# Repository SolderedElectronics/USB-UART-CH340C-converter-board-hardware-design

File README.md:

# USB-UART CH340 converter board Hardware Design

## About the Product

|  |
| :----------------------------------------------------------: |
| [Buy USB-UART CH340 converter board](https://www.solde.red/333028) |

This small USBUART adapter converts USB communication into UART (serial) communication, and everything you might need is already on this small board. In addition to the classic UART pins that are arranged in the standard layout: DTR, RXD, TXD, VCC, CTS, GND, other pins available of the CH340 chip are also available on header: RS232, RI, DCD, DSR, RST and CTS. Indication LEDs show activity on RXT and TXD lines, and a 500mA fuse protects this programmer, the USB port of the computer that is connected, and other devices connected to it from damage.

Additionally, there is a voltage regulator and a switch on the board, and it is possible to choose the output voltage of 3.3V or 5V, depending on the device you are using. The logic of the UART signal is always 3.3V, but don’t worry, 5V devices will work with 3V3 UART logic without any problems. Use a USB-C cable to connect.

---

## Repository Contents

This repository contains all design files for USB-UART CH340 converter board, organized as follows:

- **`CAD` folder**: Contains KiCAD design files, including:
  - Schematics
  - PCB layout
  - Panel PCB layout
  - Source 3D files in Fusion360, if any
  - All files are sorted by version with a detailed change log.
- **`OUTPUTS` folder**: Includes all production-ready files, such as:
  - Bill of Materials (BOM) and interactive BOM (iBOM)
  - PDF versions of schematics
  - 3D `.step` file of the board
  - 3D-printable models
  - Gerber files for PCB manufacturing
  - Image of the pinout of the board
  - Product image
  - Compliance, legal and generic sales documents

Refer to the `Change Log` in the CAD folder for details about updates between versions.

---

## Learn More About the Product

Beyond the repository, explore the following resources:

### Soldered Verify

The **Soldered Verify** system ensures every board you purchase from Soldered is fully functional. It also provides access to exclusive test data for your product. To get started, find the unique Soldered Verify ID on your product's packaging and enter the ID on the [Soldered Verify page](https://soldered.com/verify/) to access test results and additional product details.

### Soldered Community

Soldered Community is your go-to place for technical support. Our engineers track and answer all questions posted there, and it’s a great space for the maker community. Get answers to your questions and solutions for your challenges at [Soldered Community](https://soldered.com/community).

### solde.red

solde.red is an ultimate URL shortener and information hub. Access it by typing solde.red/ followed by your product SKU, e.g., [solde.red/333000](https://solde.red/333000), to find getting-started guides, datasheets, open-source hardware and software files, certifications, images, pinouts, and more. Read more about the shortener [here](https://solde.red/info/).

---

## Contributing

Contributions are welcome! Here’s how you can get involved:

- Submit pull requests to enhance the design or fix issues.
- Report bugs or problems by opening an issue.

We encourage community collaboration to make this product even better.

---

## About Soldered

[Soldered for Makers](https://soldered.com) specializes in designing and manufacturing electronic products tailored for enthusiasts, ranging from hobbyists to professionals. Our portfolio includes electronic boards, sensors, and actuators that are widely utilized in fields such as microelectronics, mechatronics, robotics, programming, and IoT. Every product we offer is designed in-house and built upon open-source hardware and software platforms. Proudly certified and manufactured within the European Union, our catalog likely includes the product you need for your project.

We complement these products with comprehensive tutorials and manuals, product descriptions, schematics, programming codes, and project examples. Our round-the-clock [customer and technical support](https://soldered.com/community) is available for all our products, irrespective of the sales channel. Soldered’s success and services reflect our maker community’s unwavering [trust](https://www.trustpilot.com/review/soldered.com), for which we are deeply grateful. Join our community and create using Soldered products.

---

## License

All Soldered open-source hardware (OSH) is under The TAPR Open Hardware License. Read more in the LICENSE file located in this repository.

**Disclaimer:**

No warranty - all designs in this repository are distributed in the hope that they will be useful, but without any warranty. They are provided "AS IS", therefore without warranty of any kind, either expressed or implied. The entire quality and performance of what you do with the contents of this repository are your responsibility. In no event Soldered Electronics will be liable for your damages, or losses, including any general, special, incidental, or consequential damage arising out of the use or inability to use the contents of this repository. 

---

## Have fun!

Thank you for your support from your fellow makers at Soldered Electronics.

Happy Making!

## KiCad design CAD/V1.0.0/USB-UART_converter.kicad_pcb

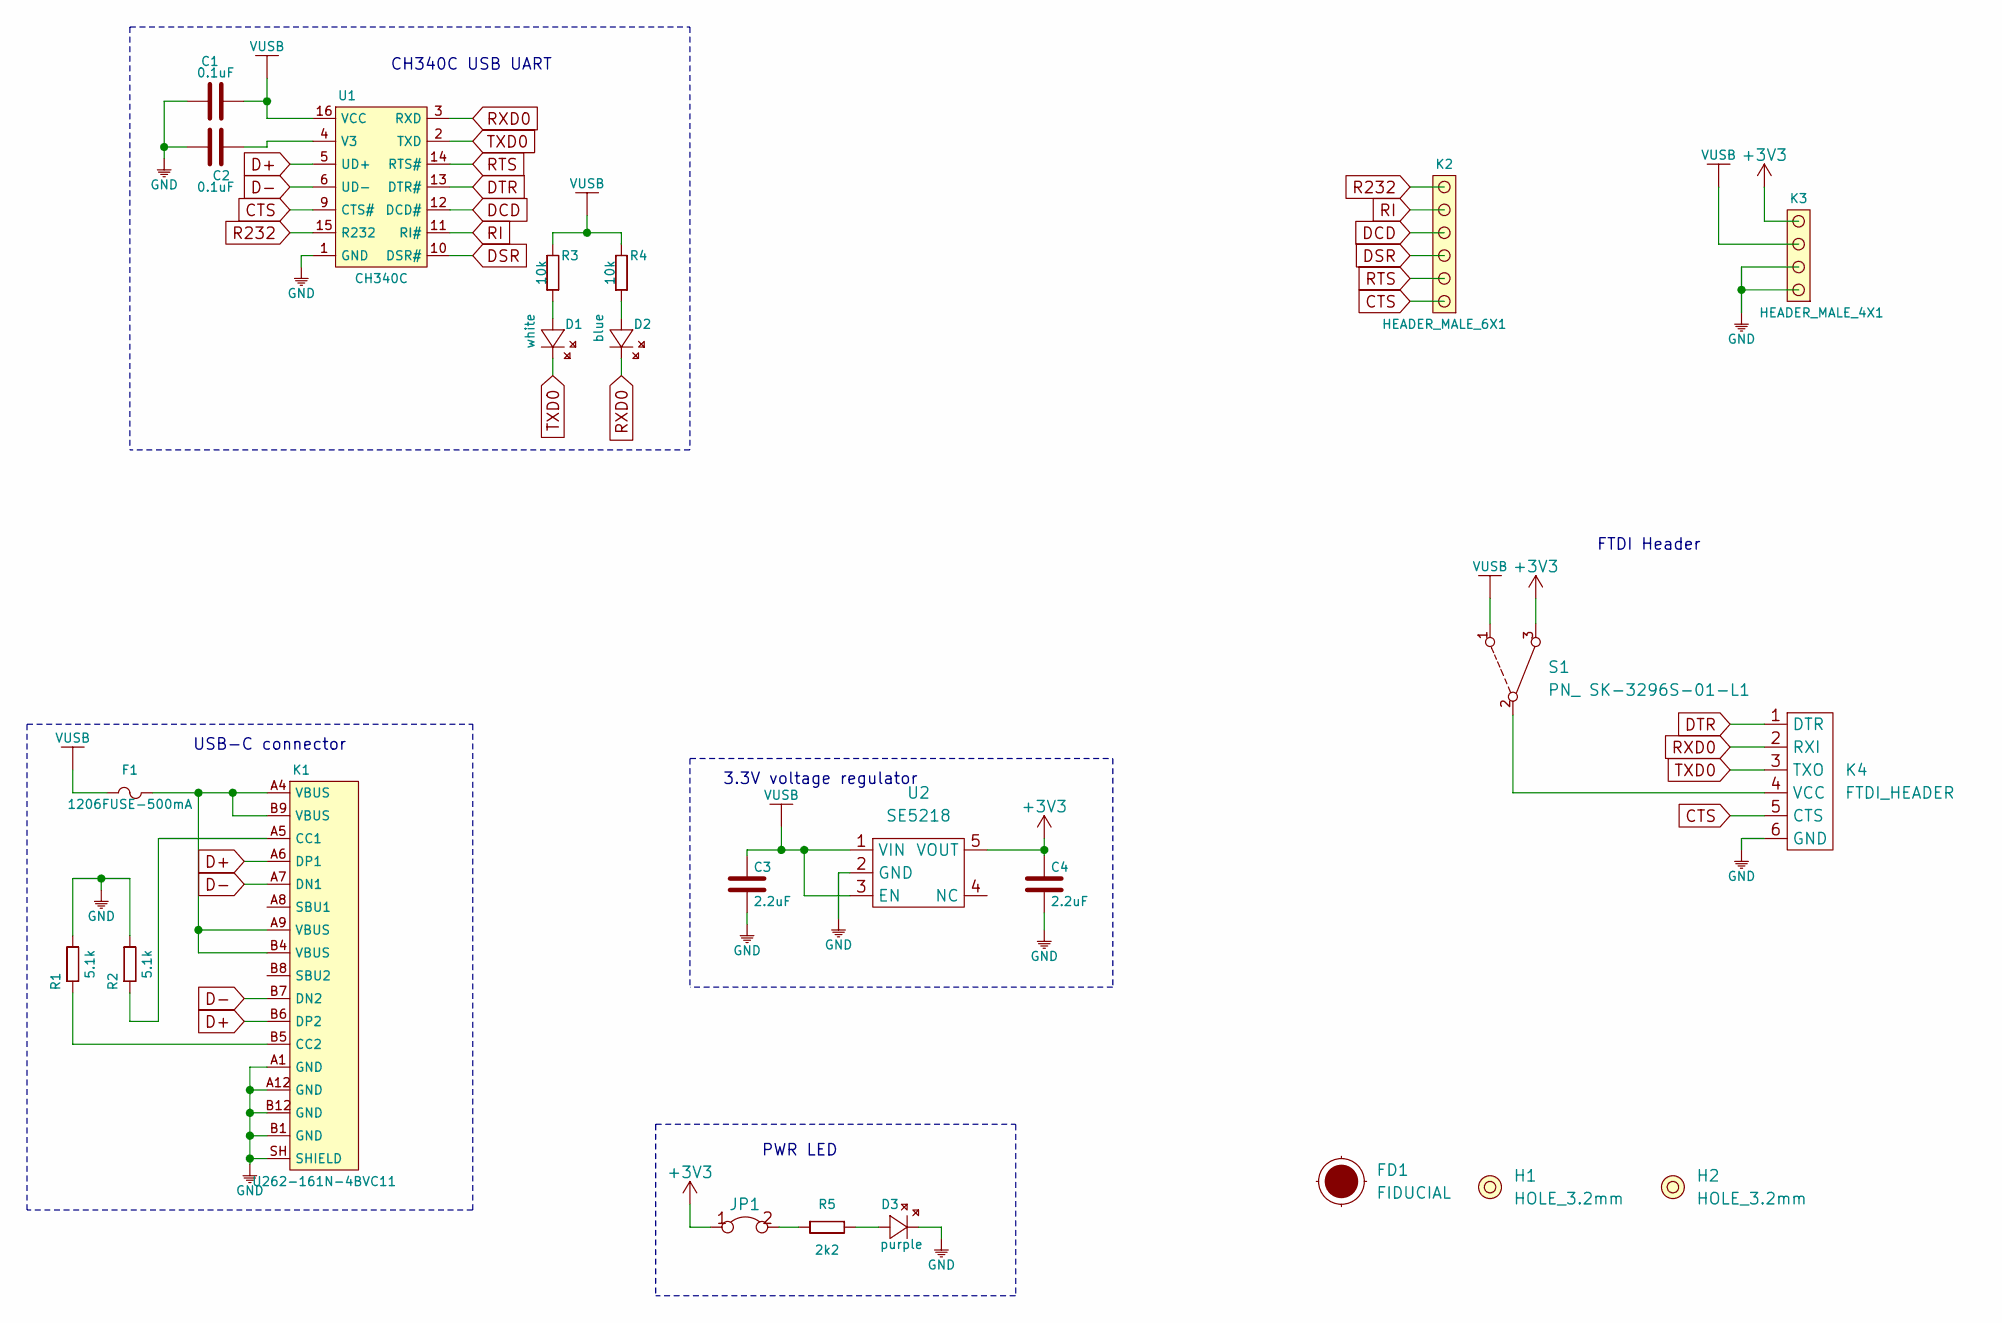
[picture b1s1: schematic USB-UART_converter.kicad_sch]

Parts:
C1, C2: 0.1uF; 0603C
C3, C4: 2.2uF; 0603C
D1: white; 0402LED
D2: blue; 0402LED
D3: purple; 0402LED
F1: 1206FUSE-500mA; 1206FUSE
FD1: FIDUCIAL; FIDUCIAL_23
H1, H2: HOLE_3.2mm
JP1: SMD-JUMPER-CONNECTED_TRACE_SLODERMASK
K1: U262-161N-4BVC11
K2: HEADER_MALE_6X1
K3: HEADER_MALE_4X1
K4: FTDI_HEADER; HEADER_MALE_6X1
R1, R2: 5.1k; 0603R
R3, R4: 10k; 0402R
R5: 2k2; 0402R
S1: PN_ SK-3296S-01-L1; SWITCH_ON_OFF_ON_3296
U1: CH340C; SOP-16
U2: SE5218; SOT-23-5

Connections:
+3V3: C4.2, JP1.1, K3.4, S1.3, U2.5 (VOUT)
CTS: K2.1, K4.5 (CTS), U1.9 (CTS#)
D+: K1.A6 (DP1), K1.B6 (DP2), U1.5 (UD+)
D-: K1.A7 (DN1), K1.B7 (DN2), U1.6 (UD-)
DCD: K2.4, U1.12 (DCD#)
DSR: K2.3, U1.10 (DSR#)
DTR: K4.1 (DTR), U1.13 (DTR#)
GND: C1.1, C2.2, C3.1, C4.1, D3.2 (K), K1.A1 (GND), K1.A12 (GND), K1.B1 (GND), K1.B12 (GND), K1.SH (SHIELD), K3.1, K3.2, K4.6 (GND), R1.2, R2.2, U1.1 (GND), U2.2 (GND)
unnamed: C2.1, U1.4 (V3)
unnamed: D1.1 (A), R3.1
unnamed: D2.1 (A), R4.1
unnamed: D3.1 (A), R5.2
unnamed: F1.2, K1.A4 (VBUS), K1.A9 (VBUS), K1.B4 (VBUS), K1.B9 (VBUS)
unnamed: K1.A5 (CC1), R2.1
unnamed: K1.B5 (CC2), R1.1
unnamed: K4.4 (VCC), S1.2
unnamed: JP1.2, R5.1
R232: K2.6, U1.15 (R232)
RI: K2.5, U1.11 (RI#)
RTS: K2.2, U1.14 (RTS#)
RXD0: D2.2 (K), K4.2 (RXI), U1.3 (RXD)
TXD0: D1.2 (K), K4.3 (TXO), U1.2 (TXD)
VUSB: C1.2, C3.2, F1.1, K3.3, R3.2, R4.2, S1.1, U1.16 (VCC), U2.1 (VIN), U2.3 (EN)

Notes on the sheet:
USB-C connector
CH340C USB UART
PWR LED
3.3V voltage regulator
FTDI Header

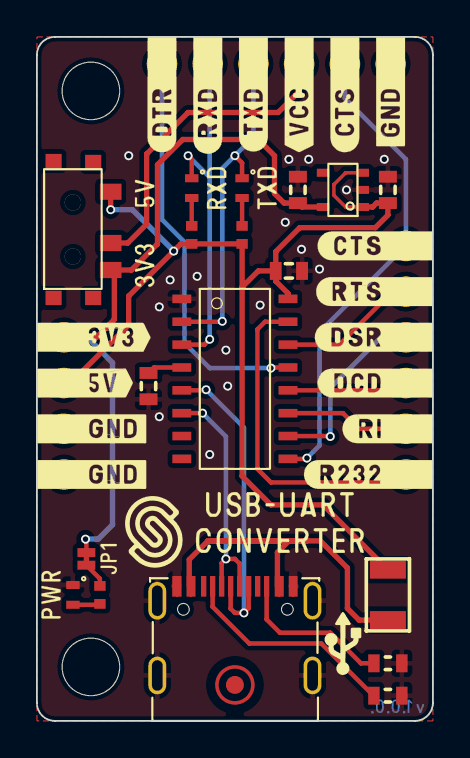
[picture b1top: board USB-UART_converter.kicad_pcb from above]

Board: 2 copper layers, 22.0 x 38.0 mm, 24 parts (0 on the bottom side), 23 nets.

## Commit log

2022-08-06 Updating open source files.
